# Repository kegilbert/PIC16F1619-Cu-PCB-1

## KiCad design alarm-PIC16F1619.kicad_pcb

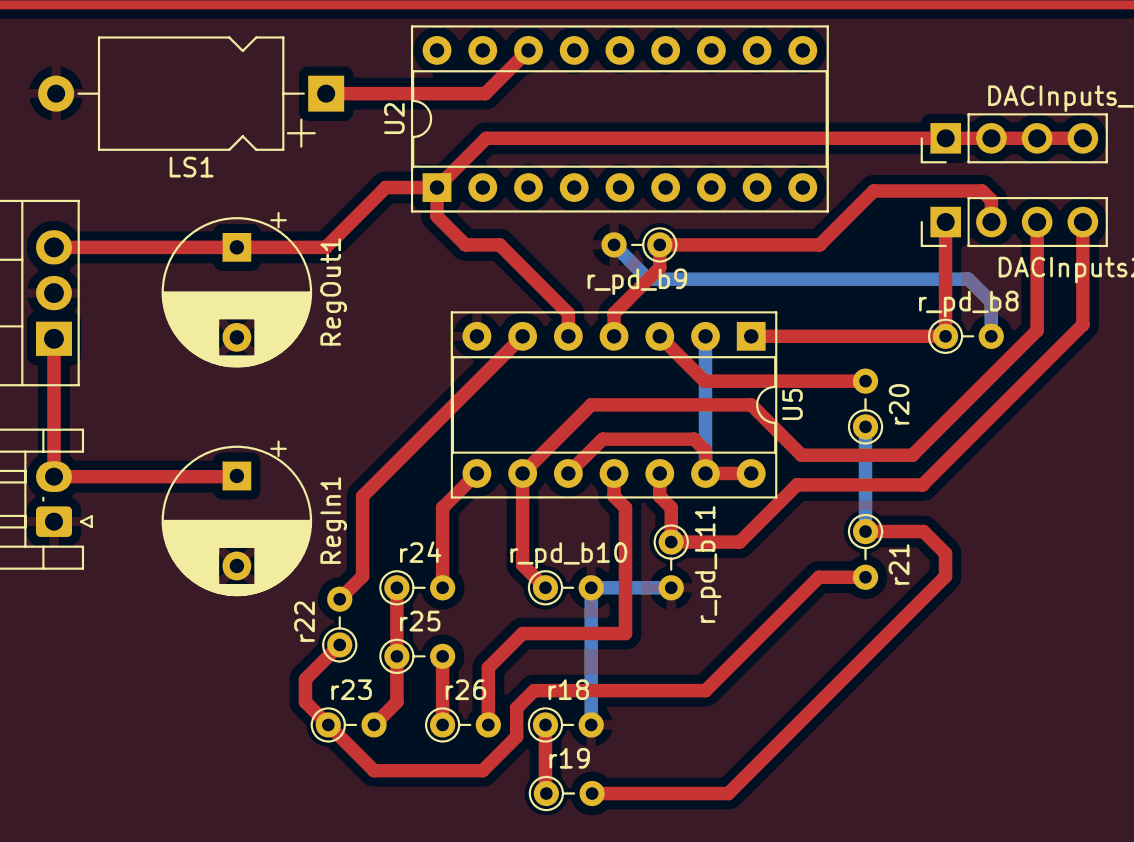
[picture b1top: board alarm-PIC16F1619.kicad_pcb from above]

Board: 2 copper layers, 22 parts (0 on the bottom side), 17 nets.

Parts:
BattIn1: Conn_01x02; JST_EH_S2B-EH_1x02_P2.50mm_Horizontal
DACInputs2: Conn_01x04_Male; PinHeader_1x04_P2.54mm_Vertical
DACInputs_+5v2: Conn_01x04_Male; PinHeader_1x04_P2.54mm_Vertical
LS1: Speaker; CP_Axial_L10.0mm_D6.0mm_P15.00mm_Horizontal
RegIn1: 33uF; CP_Radial_D8.0mm_P5.00mm
RegOut1: 33uF; CP_Radial_D8.0mm_P5.00mm
U1: L7805; TO-220-3_Vertical
U2: PIC16F1619-xP; DIP-18_W7.62mm_Socket
U5: 74LS08; DIP-14_W7.62mm_Socket
r18, r20, r22, r24, r26: 2k; R_Axial_DIN0204_L3.6mm_D1.6mm_P2.54mm_Vertical
r19, r21, r23, r25: 1k; R_Axial_DIN0204_L3.6mm_D1.6mm_P2.54mm_Vertical
r_pd_b8, r_pd_b9, r_pd_b10, r_pd_b11: 10k; R_Axial_DIN0204_L3.6mm_D1.6mm_P2.54mm_Vertical

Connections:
+5V: DACInputs_+5v2.1, DACInputs_+5v2.2, DACInputs_+5v2.3, DACInputs_+5v2.4, RegOut1.1, U1.3 (OUT), U2.1 (VDD), U5.2, U5.5, U5.10, U5.13, U5.14 (VCC)
AN0: r25.2, r26.1
GND: BattIn1.1, LS1.2, RegIn1.2, RegOut1.2, U1.2 (GND), U5.7 (GND), r18.2, r_pd_b8.2, r_pd_b9.2, r_pd_b10.2, r_pd_b11.2
unnamed: DACInputs2.1, U5.1, r_pd_b8.1
unnamed: DACInputs2.2, U5.4, r_pd_b9.1
unnamed: DACInputs2.3, U5.9, r_pd_b10.1
unnamed: DACInputs2.4, U5.12, r_pd_b11.1
unnamed: LS1.1, U2.16 (RC0)
unnamed: BattIn1.2, RegIn1.1, U1.1 (IN)
unnamed: U5.3, r20.2
unnamed: U5.6, r22.2
unnamed: U5.8, r24.2
unnamed: U5.11, r26.2
unnamed: r18.1, r19.1
unnamed: r19.2, r20.1, r21.1
unnamed: r21.2, r22.1, r23.1
unnamed: r23.2, r24.1, r25.1

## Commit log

2022-03-18 Initial Cu Mill Design
